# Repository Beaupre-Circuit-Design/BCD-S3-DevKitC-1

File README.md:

# BCD-S3-DevKitC-1

ESP32-S3-WROOM-1-N16R8 Development Board

## Description

An ESP32-S3 development board based on Espressif's ESP32-S3-DevKitC-1.

|Key Component         |Description                                                                         |
|----------------------|------------------------------------------------------------------------------------|
|ESP32-S3-WROOM-1-N16R8|ESP32-S3R8 with 3.3V, 8 MB Octal PSRAM die inside, 16 MB Quad SPI flash, PCB antenna.[^1]|
|3V3 LDO               |Power regulator that converts a 5 V supply into a 3.3 V output.|
|Boot Button           |Holding down Boot and then pressing Reset initiates Firmware Download mode for downloading firmware through the serial port.|
|Reset Button          |Press this button to restart the system.|
|RGB48 Config          |Configuration options for the RGB Led / GPIO 48.|
|USB-to-Uart Port      |A Micro-USB port used for power supply to the board, for flashing applications to the chip, as well as for communication with the chip via the on-board USB-to-UART bridge.|
|USB Port              |ESP32-S3 full-speed USB OTG interface, compliant with the USB 1.1 specification. The interface is used for power supply to the board, for flashing applications to the chip, for communication with the chip using USB 1.1 protocols, as well as for JTAG debugging.|
|UART Led              |Indicate if the USB-to-UART port is connected.|
|USB Led               |Indicate if the USB port is connected.|
|3V3 Power On          |Indicate if the 3V3 bus is powered.|
|TX Led                |Indicate if the serial bus is transmitting.|
|RX Led                |Indicate if the serial bus is receiving.|
|RGB Led               |Addressable RGB LED, driven by GPIO48.|

[^1]: GPIO35, GPIO36 and GPIO37 are used for the internal communication between ESP32-S3 and SPI flash/PSRAM memory, thus not available for external use.

## Pinout

## RGB48 Jumper

|Jumper|Effect|
|------|------|
||Default Configuration, RGB48 pin is the output of the RGBLed.|
||RGB48 pin is the output of GPIO48, Led is still active and drive by GPIO48. [^2]|
||RGB48 pin is the output of GPIO48, Led is deactivated. [^2][^3]|

[^2]: If the output of the RGBLed is still needed, a wire can be soldered to the leftmost pad.
[^3]: The RGBLed can still be driven by soldering a wire to the rightmost pad.

## Bulding / Ordering PCB

The [board layout](BCD-S3-DevKitC-1-N16R8V.production/gerber) and [bill of material](BCD-S3-DevKitC-1-N16R8V.production/assembly) has been optimised for JLCPCB's capabilities and inventories to minimise cost. The footprint for the ESP32-S3 module has been optimised for hand-soldering since this part alone greatly increase the price of the assembly.

## Version History

* 1.1(2025-02-02)
    * Fix error in RGB48 Jumper.
* 1.0(2025-01-05)
    * Initial Release.

## License

This project is licensed under the [BSD 3-Clause License](LICENSE).

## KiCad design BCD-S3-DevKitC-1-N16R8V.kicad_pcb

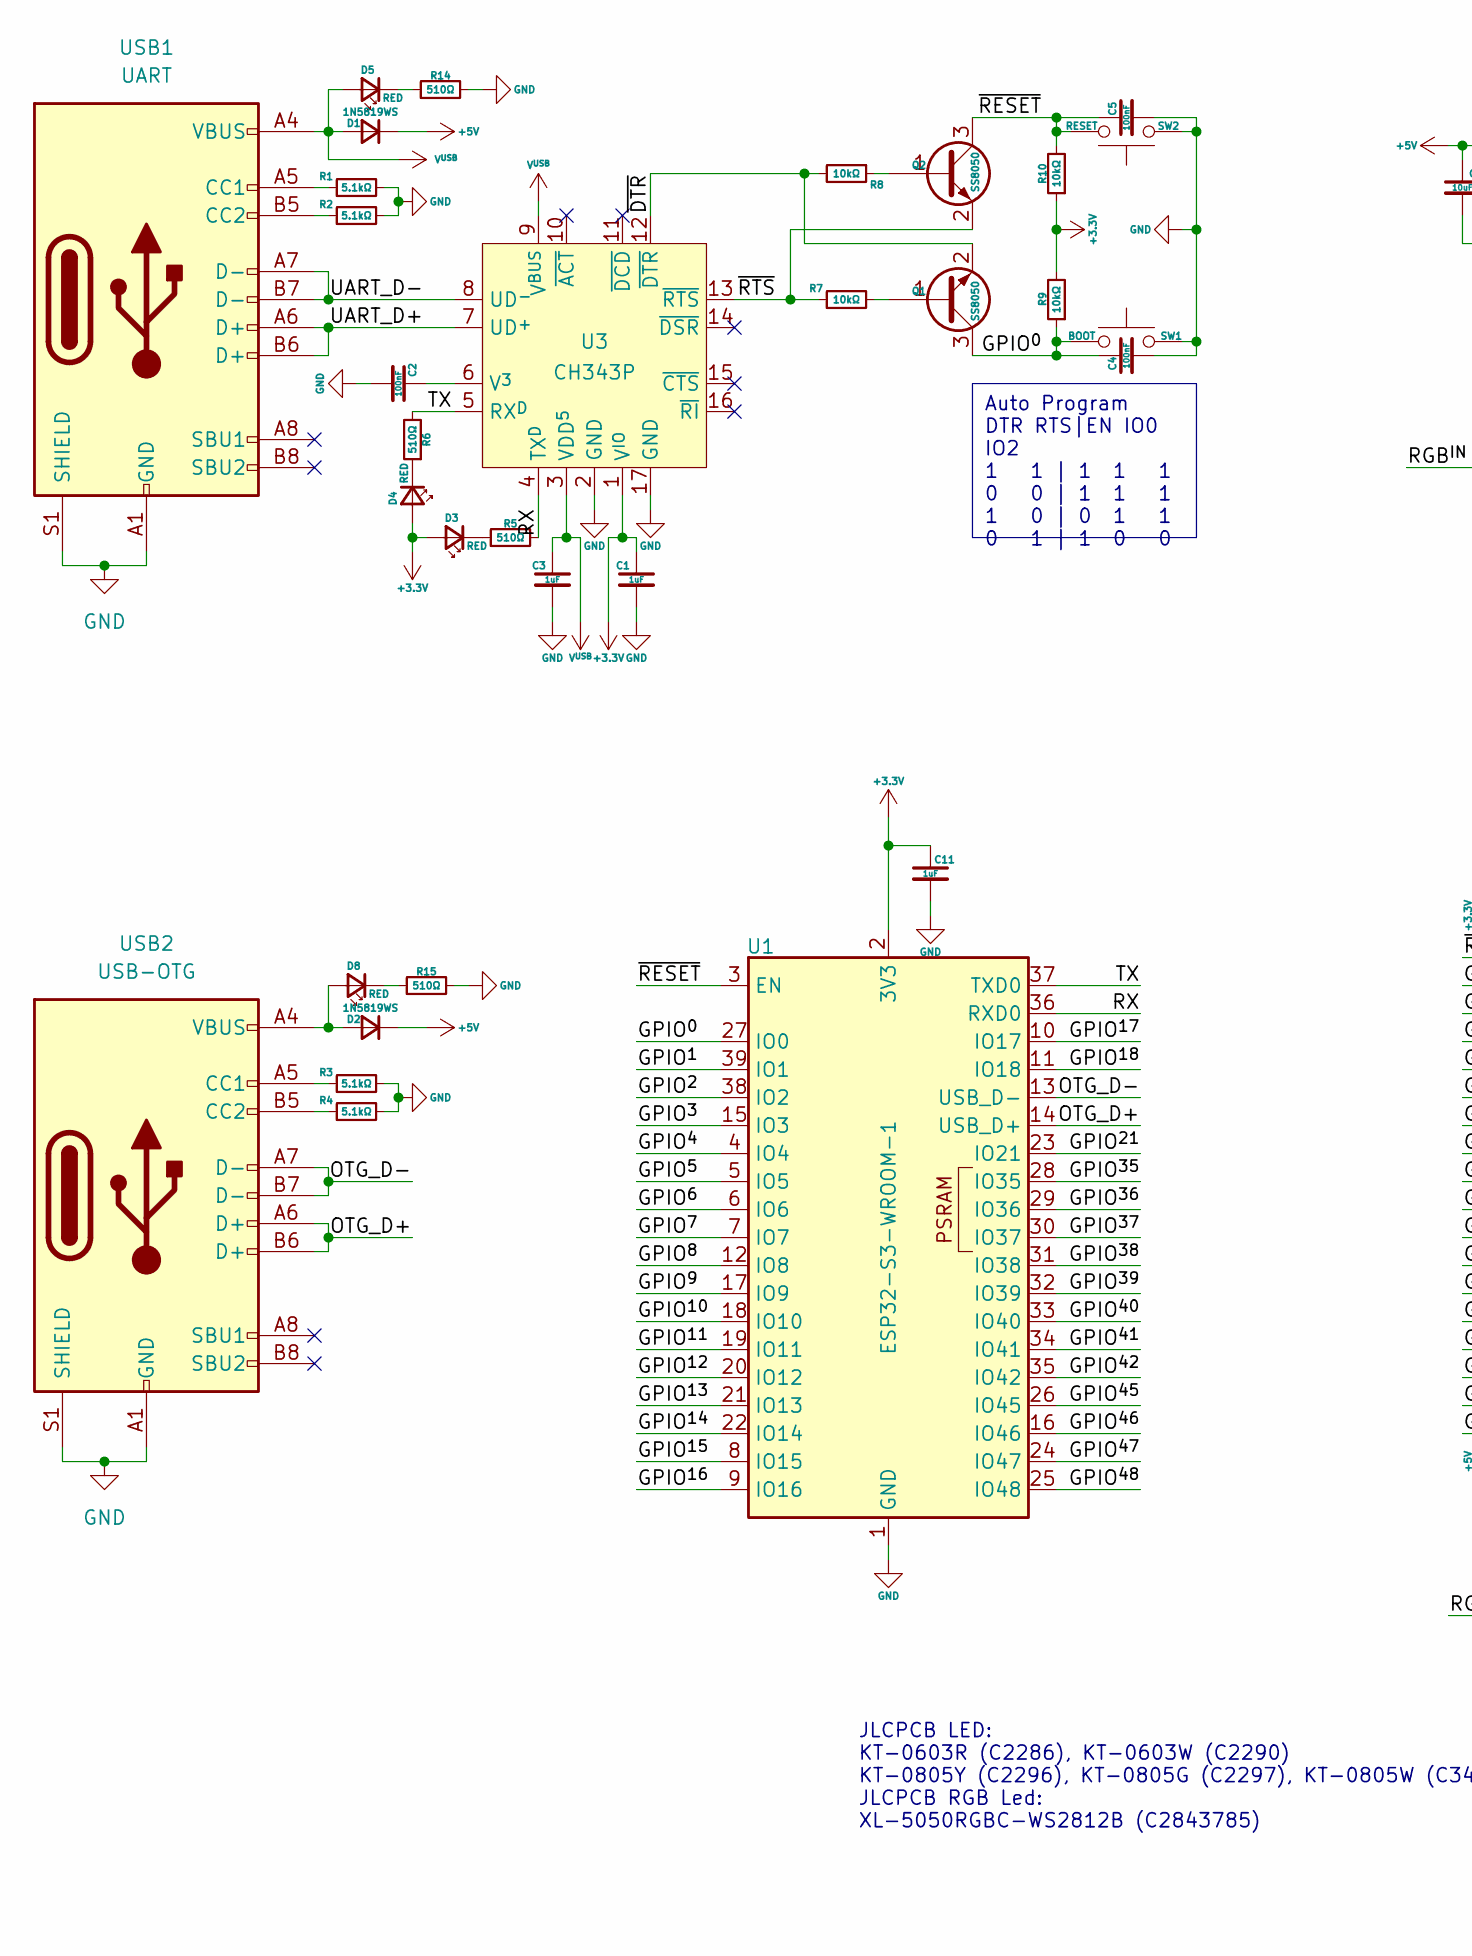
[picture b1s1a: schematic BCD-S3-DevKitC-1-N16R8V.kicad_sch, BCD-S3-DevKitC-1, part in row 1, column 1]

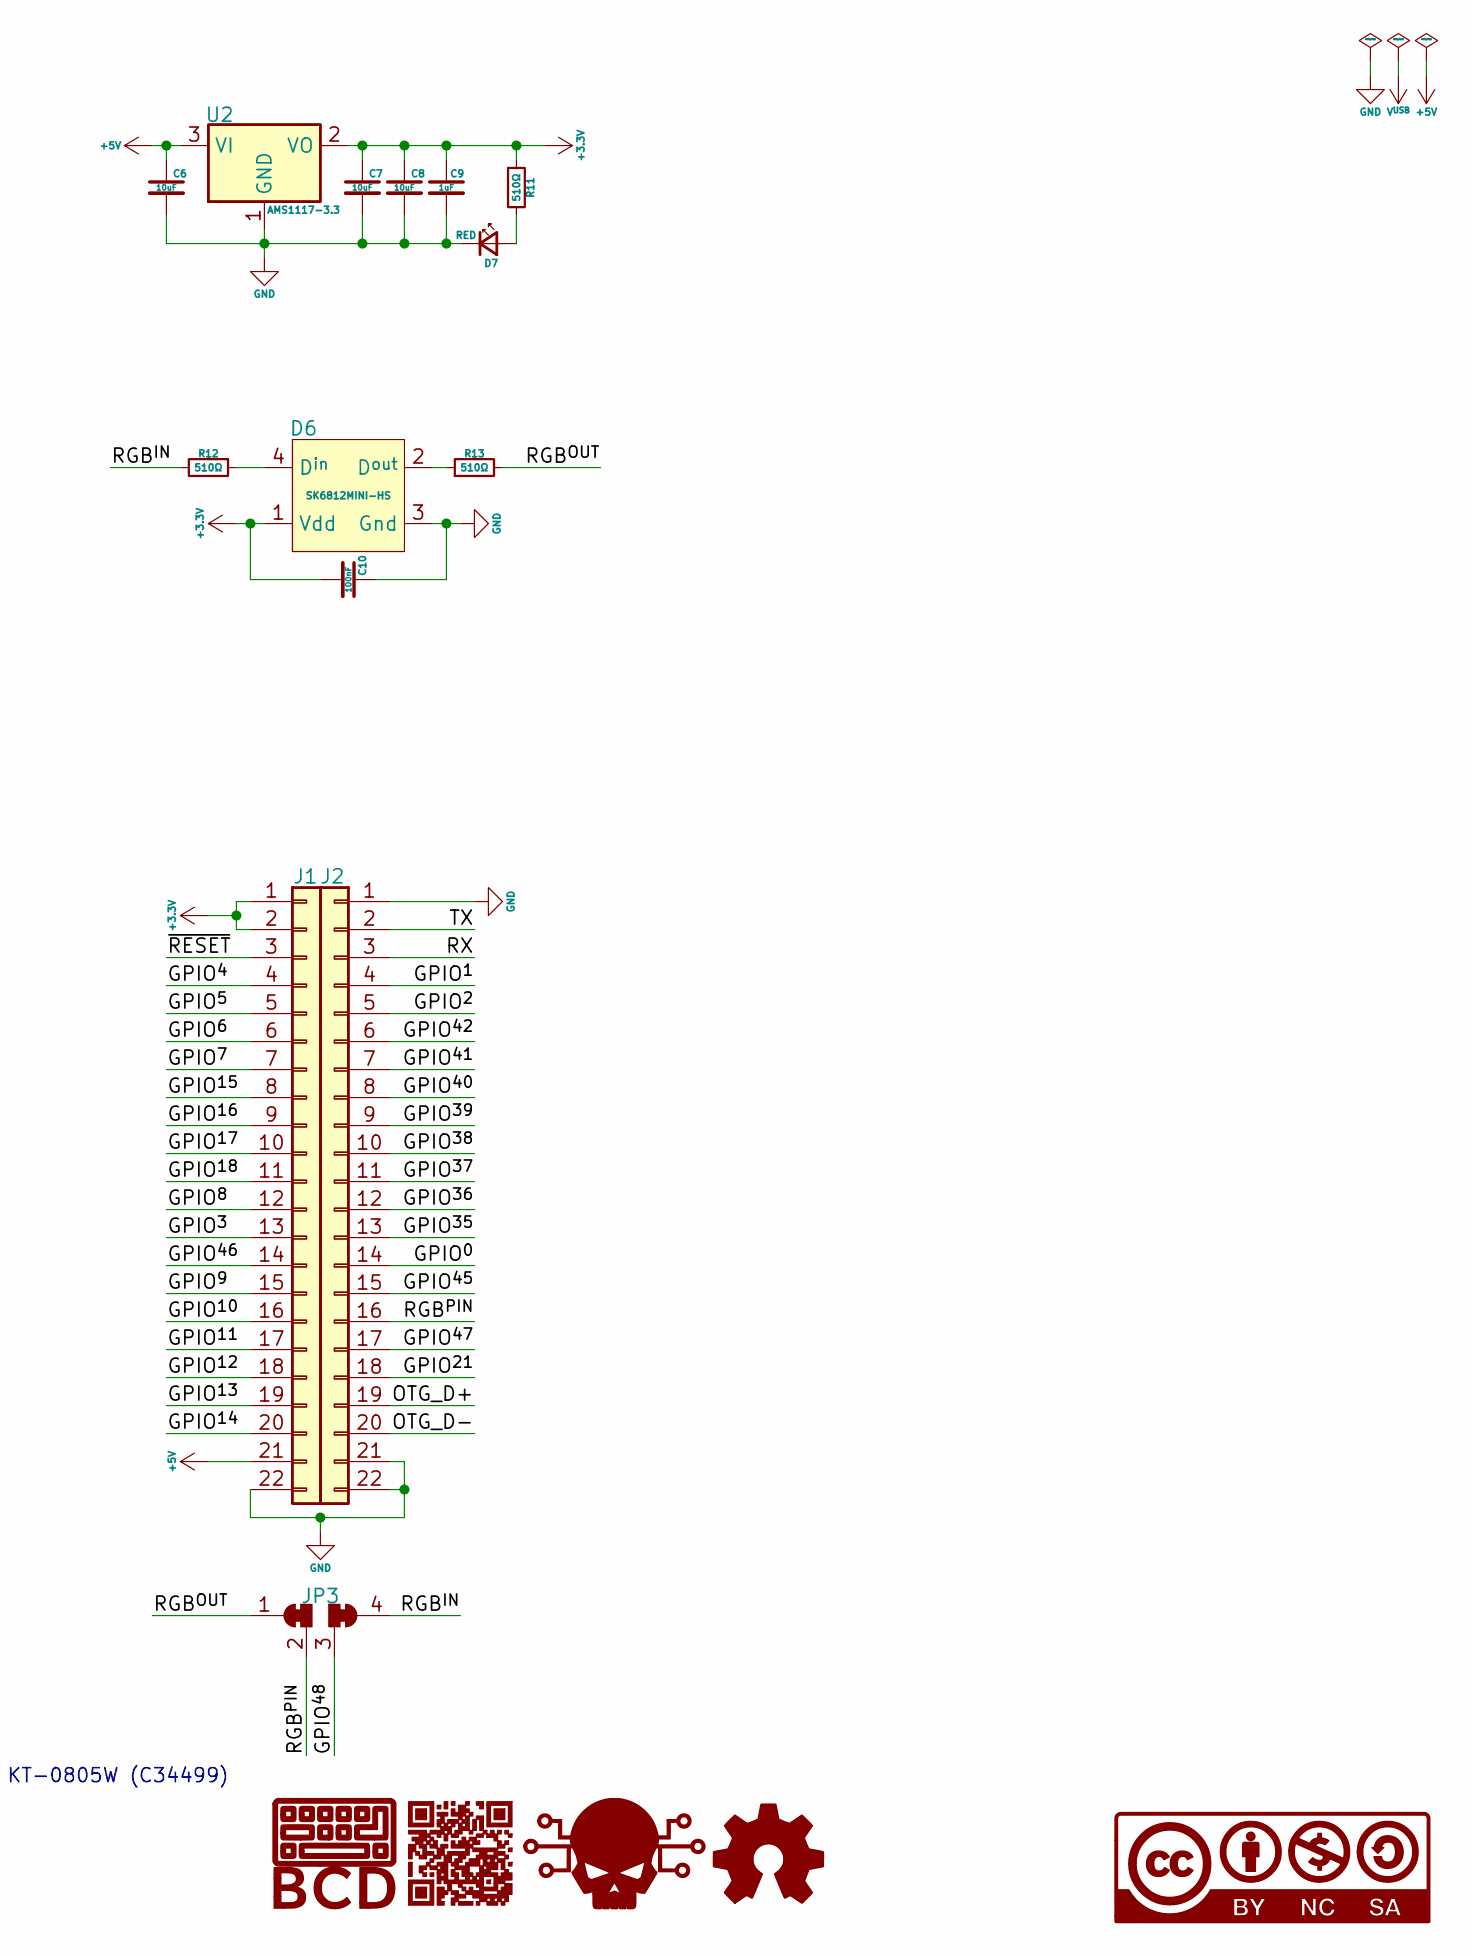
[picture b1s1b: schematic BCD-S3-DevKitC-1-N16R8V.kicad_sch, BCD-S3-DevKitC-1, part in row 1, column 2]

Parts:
C1, C3, C9, C11: 1uF; C_0402_1005Metric; PartNumber CL05A105KA5NQNC; JLCPCB C52923
C2, C4, C5, C10: 100nF; C_0402_1005Metric; PartNumber CL05B104KO5NNNC; JLCPCB C1525
C6, C7, C8: 10uF; C_0603_1608Metric; PartNumber CL10A106MA8NRNC; JLCPCB C96446
D1, D2: 1N5819WS; D_SOD-323; PartNumber 1N5819WS; JLCPCB C191023
D3, D4, D5, D7, D8: RED; LED_0603_1608Metric; PartNumber KT-0603R; JLCPCB C2286
D6: SK6812MINI-HS; PartNumber SK6812MINI-HS; JLCPCB C2922787
G1: BCD_Logo; BCD_Logo_2.5mm
G2: BDC_QR; BCD-S3-DevKitC-1_5mm
G3: Skull; Skull_2.5mm
G4: OpenSource_Hardware; Open_Source_Hardware_2.5mm
G5: CC-BY-NC-SA; cc-by-nc-sa_2.5mm
J1, J2: Conn_01x22; PinHeader_1x22_P2.54mm_Vertical
JP3: SolderJumper_4_Bridged12_34; SolderJumper-4_P1.3mm_Bridged12_34_RoundedPad1.0x1.5mm_1
Q1, Q2: SS8050; SOT-23; PartNumber SS8050(RANGE:200-350); JLCPCB C2150
R1, R2, R3, R4: 5.1kΩ; R_0402_1005Metric; PartNumber 0402WGF5101TCE; JLCPCB C25905
R5, R6, R11, R12, R13, R14, R15: 510Ω; R_0402_1005Metric; PartNumber 0402WGF5100TCE; JLCPCB C25123
R7, R8, R9, R10: 10kΩ; R_0402_1005Metric; PartNumber 0402WGF1002TCE; JLCPCB C25744
SW1: BOOT; SW_Push_1P1T_XKB_TS-1187A; PartNumber TS-1187A-B-A-B; JLCPCB C318884
SW2: RESET; SW_Push_1P1T_XKB_TS-1187A; PartNumber TS-1187A-B-A-B; JLCPCB C318884
U1: ESP32-S3-WROOM-1; ESP32-S3-WROOM-1_HandSolder; PartNumber ESP32-S3-WROOM-1-N16R8; JLCPCB C2913202
U2: AMS1117-3.3; SOT-223-3_TabPin2; PartNumber AMS1117-3.3; JLCPCB C6186
U3: CH343P; QFN-16-1EP_3x3mm_P0.5mm_EP1.7x1.7mm; PartNumber CH343P; JLCPCB C2846043
USB1: UART; USB_C_Receptacle_HRO_TYPE-C-31-M-12; PartNumber TYPE-C-31-M-12; JLCPCB C165948
USB2: USB-OTG; USB_C_Receptacle_HRO_TYPE-C-31-M-12; PartNumber TYPE-C-31-M-12; JLCPCB C165948

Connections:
+3.3V: C1.1, C7.1, C8.1, C9.1, C10.2, C11.1, D3.2 (A), D4.2 (A), D6.1 (Vdd), J1.1, J1.2, R9.2, R10.1, R11.1, U1.2 (3V3), U2.2 (VO), U3.1 (V^{IO})
+5V: C6.1, D1.1 (K), D2.1 (K), J1.21, U2.3 (VI)
/GPIO^{0}: C4.1, J2.14, Q1.3 (C), R9.1, SW1.2, U1.27 (IO0)
/GPIO^{1}: J2.4, U1.39 (IO1)
/GPIO^{2}: J2.5, U1.38 (IO2)
/GPIO^{3}: J1.13, U1.15 (IO3)
/GPIO^{4}: J1.4, U1.4 (IO4)
/GPIO^{5}: J1.5, U1.5 (IO5)
/GPIO^{6}: J1.6, U1.6 (IO6)
/GPIO^{7}: J1.7, U1.7 (IO7)
/GPIO^{8}: J1.12, U1.12 (IO8)
/GPIO^{9}: J1.15, U1.17 (IO9)
/GPIO^{10}: J1.16, U1.18 (IO10)
/GPIO^{11}: J1.17, U1.19 (IO11)
/GPIO^{12}: J1.18, U1.20 (IO12)
/GPIO^{13}: J1.19, U1.21 (IO13)
/GPIO^{14}: J1.20, U1.22 (IO14)
/GPIO^{15}: J1.8, U1.8 (IO15)
/GPIO^{16}: J1.9, U1.9 (IO16)
/GPIO^{17}: J1.10, U1.10 (IO17)
/GPIO^{18}: J1.11, U1.11 (IO18)
/GPIO^{21}: J2.18, U1.23 (IO21)
/GPIO^{35}: J2.13, U1.28 (IO35)
/GPIO^{36}: J2.12, U1.29 (IO36)
/GPIO^{37}: J2.11, U1.30 (IO37)
/GPIO^{38}: J2.10, U1.31 (IO38)
/GPIO^{39}: J2.9, U1.32 (IO39)
/GPIO^{40}: J2.8, U1.33 (IO40)
/GPIO^{41}: J2.7, U1.34 (IO41)
/GPIO^{42}: J2.6, U1.35 (IO42)
/GPIO^{45}: J2.15, U1.26 (IO45)
/GPIO^{46}: J1.14, U1.16 (IO46)
/GPIO^{47}: J2.17, U1.24 (IO47)
/GPIO^{48}: JP3.3 (D), U1.25 (IO48)
/OTG_D+: J2.19, U1.14 (USB_D+), USB2.A6 (D+), USB2.B6 (D+)
/OTG_D-: J2.20, U1.13 (USB_D-), USB2.A7 (D-), USB2.B7 (D-)
/RGB^{IN}: JP3.4 (B), R12.2
/RGB^{OUT}: JP3.1 (A), R13.2
/RGB^{PIN}: J2.16, JP3.2 (C)
/RX: J2.3, R5.2, U1.36 (RXD0), U3.4 (TX^{D})
/TX: J2.2, R6.2, U1.37 (TXD0), U3.5 (RX^{D})
/UART_D+: U3.7 (UD^{+}), USB1.A6 (D+), USB1.B6 (D+)
/UART_D-: U3.8 (UD^{-}), USB1.A7 (D-), USB1.B7 (D-)
/~DTR: Q1.2 (E), R8.2, U3.12 (~DTR)
/~RESET: C5.1, J1.3, Q2.3 (C), R10.2, SW2.2, U1.3 (EN)
/~RTS: Q2.2 (E), R7.1, U3.13 (~RTS)
GND: C1.2, C2.2, C3.2, C4.2, C5.2, C6.2, C7.2, C8.2, C9.2, C10.1, C11.2, D6.3 (Gnd), D7.1 (K), J1.22, J2.1, J2.21, J2.22, R1.2, R2.2, R3.2, R4.2, R14.2, R15.2, SW1.1, SW2.1, U1.1 (GND), U1.40 (GND), U1.41 (GND), U2.1 (GND), U3.2 (GND), U3.17 (GND), USB1.A1 (GND), USB1.A12 (GND), USB1.B1 (GND), USB1.B12 (GND), USB1.S1 (SHIELD), USB2.A1 (GND), USB2.A12 (GND), USB2.B1 (GND), USB2.B12 (GND), USB2.S1 (SHIELD)
unnamed: D2.2 (A), D8.2 (A), USB2.A4 (VBUS), USB2.A9 (VBUS), USB2.B4 (VBUS), USB2.B9 (VBUS)
unnamed: D3.1 (K), R5.1
unnamed: D4.1 (K), R6.1
unnamed: D5.1 (K), R14.1
unnamed: D6.4 (D^{in}), R12.1
unnamed: D6.2 (D^{out}), R13.1
unnamed: D7.2 (A), R11.2
unnamed: D8.1 (K), R15.1
unnamed: Q1.1 (B), R7.2
unnamed: Q2.1 (B), R8.1
unnamed: C2.1, U3.6 (V^{3})
unnamed: R1.1, USB1.A5 (CC1)
unnamed: R2.1, USB1.B5 (CC2)
unnamed: R3.1, USB2.A5 (CC1)
unnamed: R4.1, USB2.B5 (CC2)
V^{USB}: C3.1, D1.2 (A), D5.2 (A), U3.3 (VDD^{5}), U3.9 (V^{BUS}), USB1.A4 (VBUS), USB1.A9 (VBUS), USB1.B4 (VBUS), USB1.B9 (VBUS)

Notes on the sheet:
Auto Program DTR RTS|EN IO0 IO2 1 1 | 1 1 1 0 0 | 1 1 1 1 0 | 0 1 1 0 1 | 1 0 0
JLCPCB LED: KT-0603R (C2286), KT-0603W (C2290) KT-0805Y (C2296), KT-0805G (C2297), KT-0805W (C34499) JLCPCB RGB Led: XL-5050RGBC-WS2812B (C2843785)

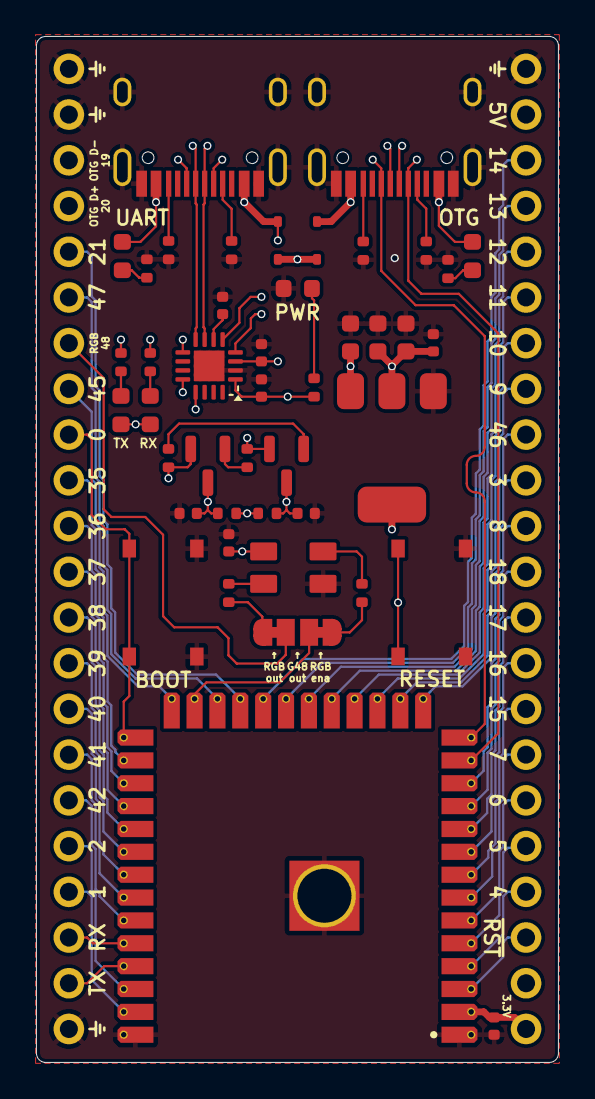
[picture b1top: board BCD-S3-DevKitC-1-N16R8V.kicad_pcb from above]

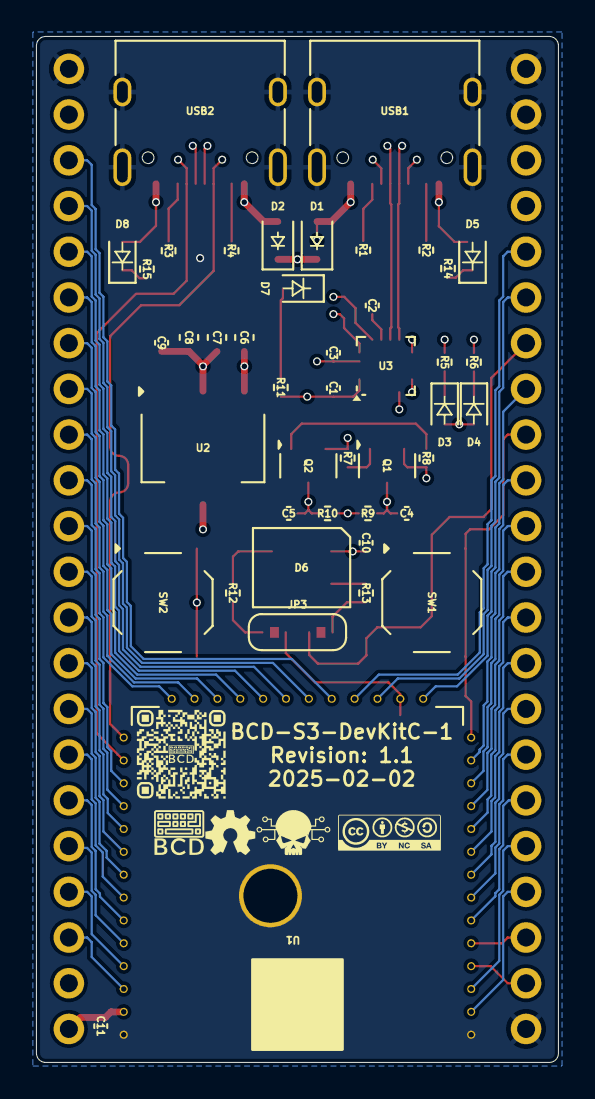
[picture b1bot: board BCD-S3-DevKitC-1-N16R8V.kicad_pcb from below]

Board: 4 copper layers, 29.0 x 57.0 mm, 51 parts (7 on the bottom side), 63 nets.

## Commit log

2025-02-02 Initial Release
2025-02-02 Fix typo
2025-02-02 Add help for RGB48 jumper. Fixed error in PCB for RGB48.
2025-02-02 Version 1.1
